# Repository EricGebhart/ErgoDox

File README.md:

# Updating keyboard layout

* Run teensy.app from teensy.dmg
* Press +L1 then teensy button
* Open newest .hex file
* Program
* Reboot

Electronics

The controller is based on a Teensy 2.0 AVR microcontroller board in the right half, with a I/O expander in the left half. The halves are connected with a 4-lead cable with power and i2c lines to the I/O expander. A mini-USB port is on the right PCB. The controller board is connected to the PCB with both pins and an internal USB cable.

The PCB design is reversible: the same type of PCB is used for both the left and right side. This means that it is possible to reverse the positions of the Teensy and the I/O expander, but then they would have to be mounted upside-down. Jumpers on the top of the PCB are also used.

The Cherry MX switches can be PCB-mounted, or be plate-mounted if a mounting plate is used (which they are in the official case designs). There is a diode for each switch, that can be either surface-mounted, through-hole, or through-hole, mounted inside most switches.

The diodes are supposed to be facing the other way on the left keyboard half, but the direction could also be swapped in firmware by flipping the values of "DRIVE_ROWS" and "DRIVE_COLUMNS" in "options.h".[1]

Component list below (adapted from [2]):

* 2	ErgoDox PCB
* 1	Teensy USB Board, Version 2.0
* 1	MCP23018-E/SP I/O expander
* 76-80	Cherry MX switches, PCB or plate-mounted
* 76-80	1N4148 diodes, SOD-123 package or DO-35 (0.3" pitch)
* 2	2.2 kΩ resistors (red, red, red)
* 3	3mm T1 LEDs
* 3	~220 Ω resistors, or match to LED. (red, red, brown)
* 5	Short jumpers
* 1	0.1 µF ceramic capacitor (marked "104" for 10*104 picofarad). Not strictly necessary
* 1	USB mini B connector WM17115.¹
* 1	USB mini B plug with short cable (such as H2955).¹
* 1	USB cable male A to male mini B.¹
* 2	3.5 mm TRRS sockets, CP-43514 but FC68129 may also work with extra pins snipped off.²
* 1	Cable with two 3.5 mm TRRS plugs.²

Notes:

1. The USB cable could also be routed directly to the Teensy 2.0, but then an additional wire has to be connected from Teensy pin VCC to the pad marked "5V" near the plug's position. GND should also be connected.

2. A fixed cable could also be used instead of TRRS cable and plugs.

Backlit version

The backlit PCB uses a single "high power" SMD mounted RGB LED on each half connected to high efficiency LED drivers controlled by PWM and I2C bus.

On top of the LED there is a light pipe which directs the light into .75mm fiber optic strands, these are then individually routed on the back of the PCB to each switch where they are fixed using the standard LED hole in the PCB/Switch.

This gives the ability for the back-light on each half to be dynamically set to any RGB value.

The development is hosted on GitHub at: [2]

The new back-light enabled PCB fixes the outermost key columns bug and is fully backwards compatible, it will function as the original when the back-light components are absent.

The following table lists the additional components required for the back light:

Existing cases can be modified for the backlit PCB by removing material to make room for the light tube.

* 2	LM3549 Sequential RGB LED drivers
* 2	LPF-R011362S 90° Light tube, square end.
* 2	LRTB C9TP RGB LEDs 30-250mA per color
* 76-80	0.75mm Fiber Optic cables, 200mm(8")
* 2	C1206C106J8RACTU 1206 Footprint 10 µF Capacitor ,6.3V/10V (X7R/X8R)
* 2	C1206C475J8NACTU 1206 Footprint 4.7 µF Capcitor ,6.3V/10V (X7R/X8R)
* 2	L1210R2R2MDWIT 1210 Footprint 2.2 µH Inductor, 1900/2000 mA

Total additional cost is expected to be between 15-20 dollars for both halves depending on volume.

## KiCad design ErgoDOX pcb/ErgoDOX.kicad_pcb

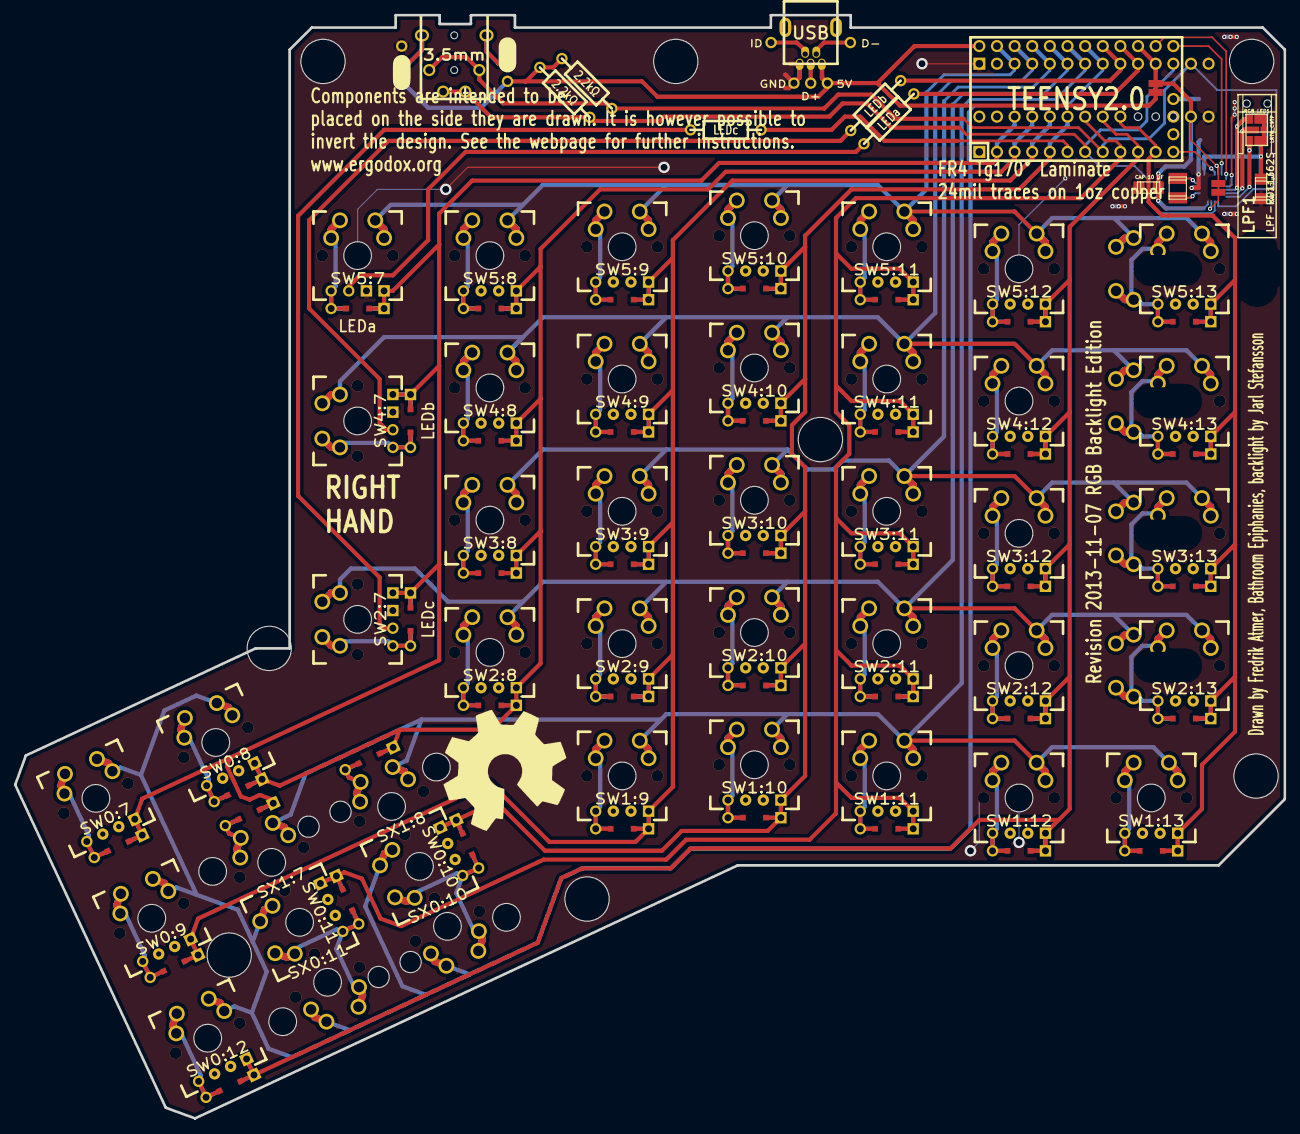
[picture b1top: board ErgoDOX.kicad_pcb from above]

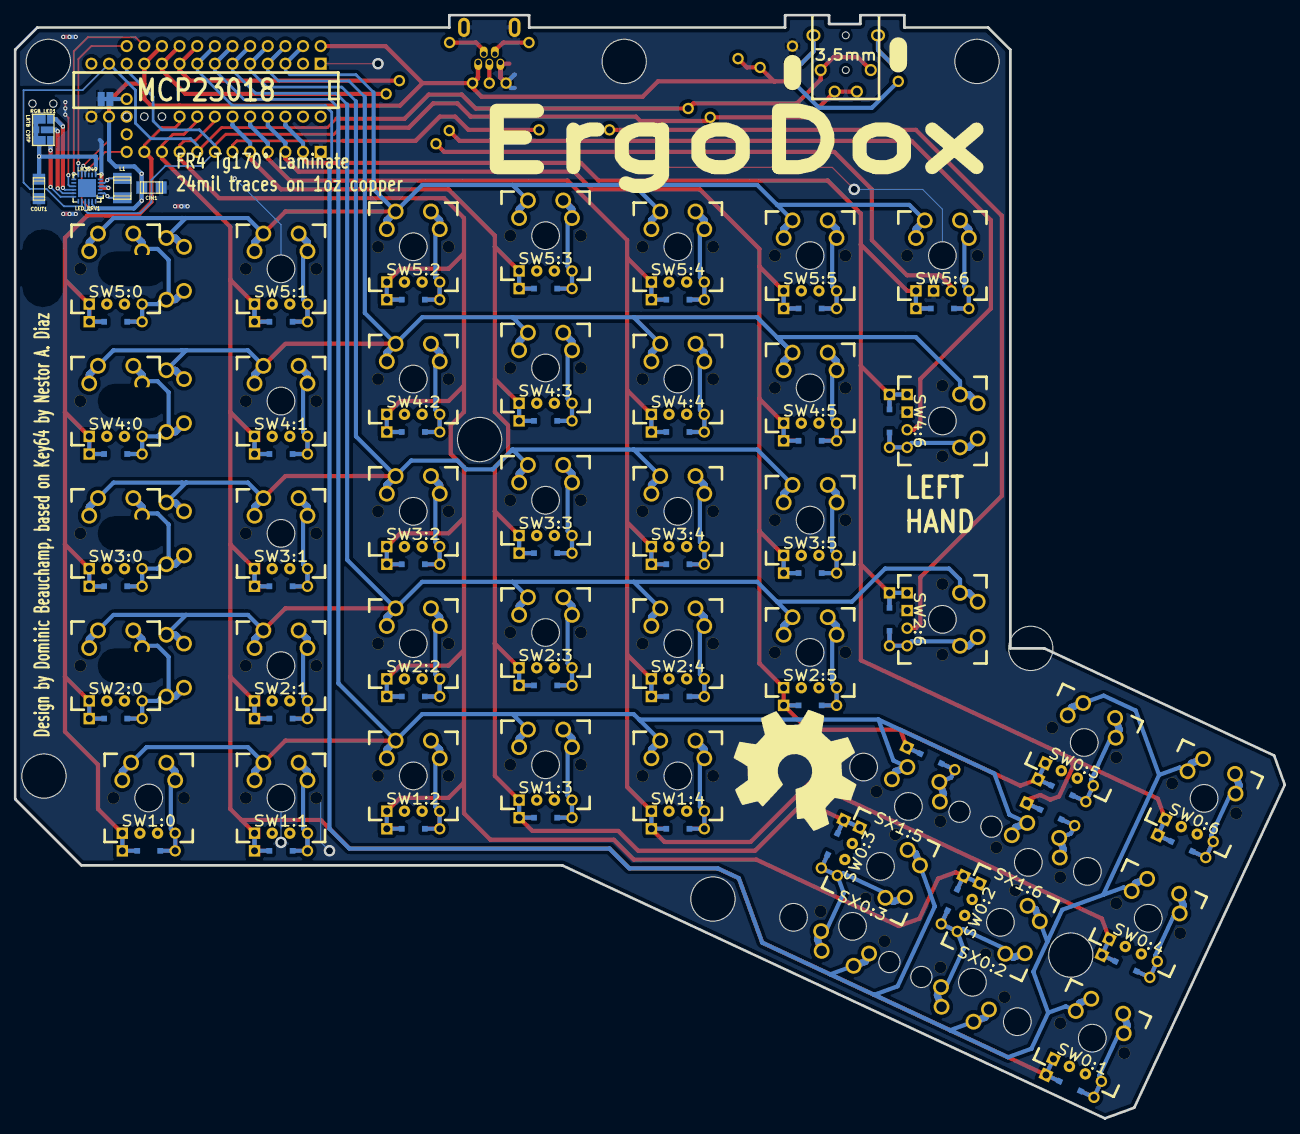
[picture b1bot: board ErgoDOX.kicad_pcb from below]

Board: 2 copper layers, 182.8 x 158.9 mm, 74 parts (8 on the bottom side), 74 nets.

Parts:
CAP 4.7 µF: COUT1; C1206C475J8NACTU
CAP 10 µF: CIN1; C1206C106J8RACTU
CIN1: CAP 10 µF; C1206C106J8RACTU
COUT1: CAP 4.7 µF; C1206C475J8NACTU
D1:7, D1:8: D; DIODE
GAP: VAL**; GAP
H99: MECHANICAL; ErgoDOXmech
J1: USB; USBMINImod
J2: 3.5mm; 4pin35mmAudio
J3, J4: JMP; 100PITCH1X3
JP1, JP2: JUMPER; GAP
L1: 2.2 µH, 1900 mA; L1210R2R2MDWIT
L1210R2R2MDWIT: L1; L1210R2R2MDWIT
LED_A1: LEDa; MX_LED
LED_B1: LEDb; MX_LED
LED_C1: LEDc; MX_LED
LED_DRV1: LM3549
LPF-R011362S: LPF1; LPF-R011362S
LRTB C9TP: RGB_LED1; LRTB_C9TP
R1, R2: 2.2kΩ; RESISTOR
RA1: LEDa; RESISTOR
RB1: LEDb; RESISTOR
RC1: LEDc; RESISTOR
RGB_LED1: LRTB_C9TP
S1, S2: STAB200; STAB_PCB940
SW0:7: SW0:6; MX_FLIP_DIODE_OPT
SW0:8: SW0:5; MX_FLIP_DIODE_OPT
SW0:9: SW0:4; MX_FLIP_DIODE_OPT
SW0:10: SW0:3; MX_FLIP_DIODE_OPT
SW0:11: SW0:2; MX_FLIP_DIODE_OPT
SW0:12: SW0:1; MX_FLIP_DIODE_OPT
SW1:9: SW1:4; MX_FLIP_DIODE_OPT
SW1:10: SW1:3; MX_FLIP_DIODE_OPT
SW1:11: SW1:2; MX_FLIP_DIODE_OPT
SW1:12: SW1:1; MX_FLIP_DIODE_OPT
SW1:13: SW1:0; MX_FLIP_DIODE_OPT
SW2:7: SW2:6; MX_FLIP_DIODE
SW2:8: SW2:5; MX_FLIP_DIODE_OPT
SW2:9: SW2:4; MX_FLIP_DIODE_OPT
SW2:10: SW2:3; MX_FLIP_DIODE_OPT
SW2:11: SW2:2; MX_FLIP_DIODE_OPT
SW2:12: SW2:1; MX_FLIP_DIODE_OPT
SW2:13: SW2:0; MX_FLIP_XX_OPT
SW3:8: SW3:5; MX_FLIP_DIODE_OPT
SW3:9: SW3:4; MX_FLIP_DIODE_OPT
SW3:10: SW3:3; MX_FLIP_DIODE_OPT
SW3:11: SW3:2; MX_FLIP_DIODE_OPT
SW3:12: SW3:1; MX_FLIP_DIODE_OPT
SW3:13: SW3:0; MX_FLIP_XX_OPT
SW4:7: SW4:6; MX_FLIP_DIODE
SW4:8: SW4:5; MX_FLIP_DIODE_OPT
SW4:9: SW4:4; MX_FLIP_DIODE_OPT
SW4:10: SW4:3; MX_FLIP_DIODE_OPT
SW4:11: SW4:2; MX_FLIP_DIODE_OPT
SW4:12: SW4:1; MX_FLIP_DIODE_OPT
SW4:13: SW4:0; MX_FLIP_XX_OPT
SW5:7: SW5:6; MX_FLIP_DIODE
SW5:8: SW5:5; MX_FLIP_DIODE_OPT
SW5:9: SW5:4; MX_FLIP_DIODE_OPT
SW5:10: SW5:3; MX_FLIP_DIODE_OPT
SW5:11: SW5:2; MX_FLIP_DIODE_OPT
SW5:12: SW5:1; MX_FLIP_DIODE_OPT
SW5:13: SW5:0; MX_FLIP_XX_OPT
SX0:10: SX0:3; MX_FLIP
SX0:11: SX0:2; MX_FLIP
SX1:7: SX1:6; MX_FLIP
SX1:8: SX1:5; MX_FLIP
U1: TEENSY2.0; TEENSY_2.0
U2: MCP23018; DIP28_300

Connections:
/B_CATHODE: LED_DRV1.18, RGB_LED1.C3
/B_EN: LED_DRV1.13, U1.19
/COL0: SW1:13.4, SW2:13.4, SW3:13.4, SW4:13.4, SW5:13.4, U1.11, U2.20
/COL1: SW0:12.4, SW1:12.4, SW2:12.4, SW3:12.4, SW4:12.4, SW5:12.4, U1.10, U2.21
/COL4: SW0:9.4, SW1:9.4, SW2:9.4, SW3:9.4, SW4:9.4, SW5:9.4, U1.4, U2.24
/COL5: D1:8.2, SW0:8.4, SW2:8.4, SW3:8.4, SW4:8.4, SW5:8.4, U1.3, U2.25
/COL6: D1:7.2, SW0:7.4, SW2:7.4, SW4:7.4, SW5:7.4, U1.2, U2.26
/COL10: SW0:10.4, SW1:10.4, SW2:10.4, SW3:10.4, SW4:10.4, SW5:10.4, U1.5, U2.23
/COL11: SW0:11.4, SW1:11.4, SW2:11.4, SW3:11.4, SW4:11.4, SW5:11.4, U1.9, U2.22
/G_CATHODE: LED_DRV1.17, RGB_LED1.C2
/G_EN: LED_DRV1.12, U1.18
/L1_T1: L1.1, LED_DRV1.2
/L2_T1: L1.2, LED_DRV1.5
/LED_A: RA1.1, U1.21
/LED_B: RB1.1, U1.22
/LED_C: RC1.1, U1.6
/ROW0: SW0:7.1, SW0:8.1, SW0:9.1, SW0:10.1, SW0:11.1, SW0:12.1, SX0:10.1, SX0:11.1, U1.23, U2.8
/ROW1: SW1:9.1, SW1:10.1, SW1:11.1, SW1:12.1, SW1:13.1, SX1:7.1, SX1:8.1, U1.24, U2.7
/ROW2: SW2:7.1, SW2:8.1, SW2:9.1, SW2:10.1, SW2:11.1, SW2:12.1, SW2:13.1, U1.25, U2.6
/ROW3: SW3:8.1, SW3:9.1, SW3:10.1, SW3:11.1, SW3:12.1, SW3:13.1, U1.26, U2.5
/ROW4: SW4:7.1, SW4:8.1, SW4:9.1, SW4:10.1, SW4:11.1, SW4:12.1, SW4:13.1, U1.27, U2.4
/ROW5: SW5:7.1, SW5:8.1, SW5:9.1, SW5:10.1, SW5:11.1, SW5:12.1, SW5:13.1, U1.28, U2.3
/R_CATHODE: LED_DRV1.16, RGB_LED1.C1
/R_EN: LED_DRV1.10, U1.12
/SCLM: J2.3, J2.5, LED_DRV1.21, R2.2, U1.7, U2.12
/SDAM: J2.2, J2.6, LED_DRV1.20, R1.2, U1.8, U2.13
/V_OUT_C_CATHODE: COUT1.2, LED_DRV1.7, RGB_LED1.A1, RGB_LED1.A2, RGB_LED1.A3
GND: CAP 4.7 µF.1, CAP 10 µF.2, CIN1.1, COUT1.1, H99.0, J1.5, J1.6, J3.3, J4.3, JP2.1, LED_A1.2, LED_B1.2, LED_C1.2, LED_DRV1.4, LED_DRV1.15, S1.0, S2.0, SW0:7.0, SW0:8.0, SW0:9.0, SW0:10.0, SW0:11.0, SW0:12.0, SW1:9.0, SW1:10.0, SW1:11.0, SW1:12.0, SW1:13.0, SW2:7.0, SW2:8.0, SW2:9.0, SW2:10.0, SW2:11.0, SW2:12.0, SW2:13.0, SW3:8.0, SW3:9.0, SW3:10.0, SW3:11.0, SW3:12.0, SW3:13.0, SW4:7.0, SW4:8.0, SW4:9.0, SW4:10.0, SW4:11.0, SW4:12.0, SW4:13.0, SW5:7.0, SW5:8.0, SW5:9.0, SW5:10.0, SW5:11.0, SW5:12.0, SW5:13.0, SX0:10.0, SX0:11.0, SX1:7.0, SX1:8.0, U1.1, U1.15, U2.1, U2.15
unnamed: J2.1, J3.2
unnamed: J2.4, J4.2
unnamed: SW1:9.2, SW1:9.3
unnamed: SW0:10.2, SW0:10.3, SX0:10.2
unnamed: SW0:7.2, SW0:7.3
unnamed: SW2:13.2, SW2:13.3
unnamed: SW2:10.2, SW2:10.3
unnamed: SW2:11.2, SW2:11.3
unnamed: SW1:11.2, SW1:11.3
unnamed: SW1:10.2, SW1:10.3
unnamed: SW2:12.2, SW2:12.3
unnamed: SW1:13.2, SW1:13.3
unnamed: SW1:12.2, SW1:12.3
unnamed: SW0:12.2, SW0:12.3
unnamed: SW0:9.2, SW0:9.3
unnamed: SW0:8.2, SW0:8.3
unnamed: D1:7.1, SX1:7.2
unnamed: D1:8.1, SX1:8.2
unnamed: SW3:10.2, SW3:10.3
unnamed: SW5:12.2, SW5:12.3
unnamed: SW5:13.2, SW5:13.3
unnamed: SW4:13.2, SW4:13.3
unnamed: SW3:13.2, SW3:13.3
unnamed: SW3:12.2, SW3:12.3
unnamed: SW3:11.2, SW3:11.3
unnamed: SW4:12.2, SW4:12.3
unnamed: SW3:9.2, SW3:9.3
unnamed: SW3:8.2, SW3:8.3
unnamed: SW2:7.2, SW2:7.3
unnamed: SW2:8.2, SW2:8.3
unnamed: SW2:9.2, SW2:9.3
unnamed: SW5:9.2, SW5:9.3
unnamed: SW5:7.2, SW5:7.3
unnamed: SW4:7.2, SW4:7.3
unnamed: SW4:8.2, SW4:8.3
unnamed: SW5:8.2, SW5:8.3
unnamed: SW5:10.2, SW5:10.3
unnamed: SW4:10.2, SW4:10.3
unnamed: SW4:9.2, SW4:9.3
unnamed: SW5:11.2, SW5:11.3
unnamed: SW4:11.2, SW4:11.3
unnamed: LED_C1.1, RC1.2
unnamed: LED_B1.1, RB1.2
unnamed: LED_A1.1, RA1.2
unnamed: SW0:11.2, SW0:11.3, SX0:11.2
VCC: CIN1.2, J1.1, J3.1, J4.1, JP1.1, LED_DRV1.11, LED_DRV1.22, LED_DRV1.23, R1.1, R2.1, U1.20, U1.29, U2.11, U2.16

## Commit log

2013-11-10 Add modules for LED
2013-11-11 More updates for backlight
2013-11-11 LED now available on both sides
2013-11-13 Fixed grounding issues and masks
2013-11-13 AlmostReady
2013-11-13 FinalCut
2013-11-14 Fixed Soldermask
2013-11-16 Fixed optional switch locations
    Fixed (1x) optional locations for outermost column.
2013-11-16 Fixed gerber files with correct switch locations.
2013-11-16 Added info on hardware
2013-11-17 Fixed tracks around secondary outer most column
2013-11-18 Allow output cap for led driver on either side.
    Otherwise it might interfere with light tube.
    Also fixed ground connection for all caps.
2013-11-26 Fixed last switch secondary switch pos.
2013-11-29 Allow dual side caps and inductor
2013-11-29 Fix various backlight things
2013-11-29 Polish some connections
2013-12-02 Re-Added through hole for fibers
2013-12-02 Repl. Star w. OSS HW Logo
2013-12-07 Add merged drill file, update graphics
2013-12-09 Added I2C debugging Arduino projects
2013-12-09 Skeleton with notes on operation
2013-12-09 Inital read registers
2013-12-09 Working Again
2013-12-10 Updates to tests
2013-12-16 Remove old dysfunctional test code, add new code.
2013-12-18 Added Rhino3D Model of Lister Case.
    Fixed a lot of minor issues and open curves.
